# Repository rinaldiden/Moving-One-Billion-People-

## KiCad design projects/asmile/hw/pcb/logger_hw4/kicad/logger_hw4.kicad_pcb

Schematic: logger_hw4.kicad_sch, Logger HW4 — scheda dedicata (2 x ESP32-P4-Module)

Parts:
BZ1: buzzer attivo 3-7V; BUZ-SMD_L9.6-W9.6-LS10.0-R; LCSC C96127
C1, C2, C5, C8: 10u; C_0805_2012Metric; LCSC C15850
C3, C11, C21, C81, C91, C100, C101: 100n; C_0402_1005Metric; LCSC C1525
C4: 100n; C_0402_1005Metric; LCSC C1525; not fitted
C6, C7, C9, C10, C13, C20: 22u; C_0805_2012Metric; LCSC C45783
C12, C22, C37, C82, C92: 1u; C_0603_1608Metric; LCSC C1592
C36: 100n 50V; C_0603_1608Metric; LCSC C14663
C60, C70: 10u; C_0603_1608Metric; LCSC C19702
C80, C90: 4.7u; C_0402_1005Metric; LCSC C23733
D1: 1N4148W; SOD-123F_L2.7-W1.6-LS3.8-RD; LCSC C81598
D2: rosso; LED_0603_1608Metric; LCSC C2286
D3: verde; LED_0603_1608Metric; LCSC C12624
D4: blu (B); LED_0603_1608Metric; LCSC C2288
D5: SS34; SMA_L4.2-W2.6-LS5.0-RD_1; LCSC C8678
D6: SMF5.0A; SOD-123FL_L2.7-W1.8-LS3.8-RD; LCSC C193402
D8: SS14; SMA_L4.2-W2.6-LS5.0-RD_1; LCSC C2480
H1, H2, H3, H4: M2.5; MountingHole_2.7mm_M2.5
H11, H12, H13, H14, H15, H16, H17, H18: M2 camera; MountingHole_2.2mm_M2
J1: USB-C (carica + flash A); USB-C_SMD-TYPE-C-31-M-12_1; LCSC C165948
J2: BATT 1S 3 poli (+, NTC, -); CONN-SMD_S3B-PH-SM4-TB-LF-SN; LCSC C265101
J3: INTERRUTTORE est. (2 poli); CONN-SMD_PH-2AWT; LCSC C2763693
J11, J21: u.FL (piano B); RF-SMD_FRF05002-JSS103M; LCSC C88374; not fitted
J12: DEBUG A (UART0 37/38 + EN + BOOT, pogo); PinHeader_1x06_P2.54mm_Vertical; not fitted
J22: PROG B (UART0 37/38 + EN + BOOT, pogo); PinHeader_1x06_P2.54mm_Vertical; not fitted
J60: CAM SX FFC 15p 1mm; CONN-SMD_15P-P1.00_SHOU-HAN_1.0MM-15P-LT; LCSC C7529394
J61: TRIG A; CONN-SMD_2P-P1.00_SM02B-SRSS-TB-LF-SN; LCSC C160402
J70: CAM DX FFC 15p 1mm; CONN-SMD_15P-P1.00_SHOU-HAN_1.0MM-15P-LT; LCSC C7529394
J71: TRIG B; CONN-SMD_2P-P1.00_SM02B-SRSS-TB-LF-SN; LCSC C160402
J80: microSD A; TF-SMD_TF-015; LCSC C113206
J90: microSD B; TF-SMD_TF-015; LCSC C113206
J100: ESPANSIONE A; PinHeader_1x06_P2.54mm_Vertical; not fitted
L1, L2: 2.2u 4.5A; IND-SMD_L4.4-W4.2; LCSC C408335
Q1: FS8205A; SOT-23-6_L2.9-W1.6-P0.95-LS2.8-BL; LCSC C2830320
Q2: S8050; SOT-23_L2.9-W1.3-P1.90-LS2.4-BR; LCSC C2146
Q3, Q8, Q9: AO3401A; SOT-23-3_L3.0-W1.7-P0.95-LS2.9-BR; LCSC C15127
R1, R2: 5.1k; R_0402_1005Metric; LCSC C25905
R3, R4, R81, R91: 22; R_0402_1005Metric; LCSC C25092
R5: 1.2k; R_0402_1005Metric; LCSC C25862
R6, R35, R40, R41, R43, R44, R63, R73, R80, R82, R83, R84, R85, R86, R90, R92, R93, R94, R95, R96: 10k; R_0402_1005Metric; LCSC C25744
R7: 6.8k; R_0402_1005Metric; LCSC C25917
R8, R60, R70: 100; R_0402_1005Metric; LCSC C25076
R9, R50, R51, R52, R53, R54, R55, R100, R102, R103, R104: 1k; R_0402_1005Metric; LCSC C11702
R10, R13, R18, R20, R32, R101: 100k; R_0402_1005Metric; LCSC C25741
R11: 33k; R_0402_1005Metric; LCSC C25779
R12: 68k; R_0402_1005Metric; LCSC C36871
R19, R21: 22k; R_0402_1005Metric; LCSC C25768
R30, R33: 0; R_0402_1005Metric; LCSC C17168
R31, R34, R42, R45: 0; R_0402_1005Metric; LCSC C17168; not fitted
R36: 0 (PTC/perla); R_0805_2012Metric; LCSC C17477
R61, R62, R71, R72: 4.7k; R_0402_1005Metric; LCSC C25900
R110, R111, R112, R113, R114: 33; R_0402_1005Metric; LCSC C25105
RT1: NTC 10k B3950; R0805; LCSC C51597
SW1: BOOT A; SW-SMD_4P-L5.1-W5.1-P3.70-LS6.5-TL_H1.5; LCSC C318884
SW2: RESET A; SW-SMD_4P-L5.1-W5.1-P3.70-LS6.5-TL_H1.5; LCSC C318884
TP1: VBUS; TestPoint_Pad_D1.5mm
TP2: BATP; TestPoint_Pad_D1.5mm
TP3: VSYS; TestPoint_Pad_D1.5mm
TP4: 3V3_A; TestPoint_Pad_D1.5mm
TP5: 3V3_B; TestPoint_Pad_D1.5mm
TP6: GND; TestPoint_Pad_D1.5mm
TP7: VSYS_IN; TestPoint_Pad_D1.5mm
TP11: C6_RXD_A; TestPoint_Pad_D1.5mm
TP12: C6_TXD_A; TestPoint_Pad_D1.5mm
TP13: C6_BOOT_A; TestPoint_Pad_D1.5mm
TP21: C6_RXD_B; TestPoint_Pad_D1.5mm
TP22: C6_TXD_B; TestPoint_Pad_D1.5mm
TP23: C6_BOOT_B; TestPoint_Pad_D1.5mm
TP30: USB_DM_B; TestPoint_Pad_D1.5mm
TP31: USB_DP_B; TestPoint_Pad_D1.5mm
TP40: SYNC; TestPoint_Pad_D1.5mm
TP41: TRIG; TestPoint_Pad_D1.5mm
U1: USBLC6-2SC6; SOT-23-6_L2.9-W1.6-P0.95-LS2.8-BL; LCSC C2827654
U2: TP4056; ESOP-8_L4.9-W3.9-P1.27-LS6.0-BL-EP; LCSC C725790
U3: DW01A; SOT-23-6_L2.9-W1.6-P0.95-LS2.8-BR; LCSC C351410
U4, U5: TLV62569DBVR; SOT-23-5_L3.0-W1.7-P0.95-LS2.8-BR; LCSC C141836
U6: LSM6DS3TR-C; LGA-14_L3.0-W2.5-P0.50-TL; LCSC C967633
U7: AW32901 OVP 5,95 V; FCQFN-12_1.3x1.8mm_P0.4mm_AW32901; LCSC C407920
U10, U20: Waveshare ESP32-P4-Module (IPEX); Waveshare_ESP32-P4-Module

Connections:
3V3_A: C6.1, C7.1, C10.1, C11.1, C60.1, C100.1, C101.1, J12.6, J60.15, J100.1, L1.2, Q8.2 (S), R6.2, R18.1, R40.1, R41.1, R61.2, R62.2, R63.2, R80.2, TP4.1, U6.5 (VDDIO), U6.8 (VDD), U6.12 (CS), U10.84 (VBAT), U10.85 (ESP_3V3), U10.86 (ESP_3V3)
3V3_B: C9.1, C13.1, C20.1, C21.1, C70.1, J22.6, J70.15, L2.2, Q9.2 (S), R20.1, R43.1, R44.1, R71.2, R72.2, R73.2, R90.2, TP5.1, U20.84 (VBAT), U20.85 (ESP_3V3), U20.86 (ESP_3V3)
ANT_A: R42.1, U10.2 (LNA_OUT)
ANT_B: R45.1, U20.2 (LNA_OUT)
ANT_UFL_A: J11.1 (SIG), R42.2
ANT_UFL_B: J21.1 (SIG), R45.2
BATP: C2.1, J2.1, Q3.3 (D), R8.1, R10.1, TP2.1, U2.5 (BAT)
BATT_ADC: C4.1, R10.2, R11.1, U10.29 (GPIO20)
BAT_N: C3.2, J2.3, Q1.1 (S1), U3.6 (GND)
BOOT_A: J12.5, R41.2, SW1.1 (A), SW1.2 (B), U10.62 (GPIO35)
BOOT_B: J22.5, R44.2, R55.2, U20.62 (GPIO35)
BUZZER: R100.1, U10.54 (GPIO27)
BUZ_BASE: Q2.1 (B), R100.2, R101.1
BUZ_K: BZ1.2, D1.2 (A), Q2.3 (C)
B_BOOT_CTL: R55.1, U10.77 (GPIO49)
B_EN_CTL: R54.1, U10.60 (GPIO33)
B_PWR_EN: R31.1, U10.21 (GPIO6)
C6_BOOT_A: TP13.1, U10.9 (C6_IO9)
C6_BOOT_B: TP23.1, U20.9 (C6_IO9)
C6_RXD_A: TP11.1, U10.4 (C6_U0RXD)
C6_RXD_B: TP21.1, U20.4 (C6_U0RXD)
C6_TXD_A: TP12.1, U10.5 (C6_U0TXD)
C6_TXD_B: TP22.1, U20.5 (C6_U0TXD)
CAM_EN_A: J60.11, R63.1, U10.26 (GPIO11)
CAM_EN_B: J70.11, R73.1, U20.26 (GPIO11)
CC1: J1.A5 (CC1), R1.1
CC2: J1.B5 (CC2), R2.1
CHRG_N: R6.1, U2.7 (~CHRG), U10.53 (GPIO26)
CSI_CKN_A: J60.8, U10.44 (CSI_CLKN)
CSI_CKN_B: J70.8, U20.44 (CSI_CLKN)
CSI_CKP_A: J60.9, U10.43 (CSI_CLKP)
CSI_CKP_B: J70.9, U20.43 (CSI_CLKP)
CSI_D0N_A: J60.2, U10.41 (CSI_DATAN0)
CSI_D0N_B: J70.2, U20.41 (CSI_DATAN0)
CSI_D0P_A: J60.3, U10.42 (CSI_DATAP0)
CSI_D0P_B: J70.3, U20.42 (CSI_DATAP0)
CSI_D1N_A: J60.5, U10.45 (CSI_DATAN1)
CSI_D1N_B: J70.5, U20.45 (CSI_DATAN1)
CSI_D1P_A: J60.6, U10.46 (CSI_DATAP1)
CSI_D1P_B: J70.6, U20.46 (CSI_DATAP1)
EN_A: C12.1, J12.4, R40.2, SW2.1 (A), SW2.2 (B), U10.87 (ESP_EN)
EN_B: C22.1, J22.4, R43.2, R54.2, U20.87 (ESP_EN)
EN_BUCK_B: R30.2, R31.2, R32.1, U5.1 (EN)
EXP_IO1: J100.2, U10.16 (GPIO1)
EXP_IO47: J100.3, U10.75 (GPIO47)
EXP_IO48: J100.4, U10.76 (GPIO48)
FB_A: R18.2, R19.1, U4.5 (FB)
FB_B: R20.2, R21.1, U5.5 (FB)
GATE_Q3: D8.1 (K), Q3.1 (G), R35.1
GND: C1.2, C2.2, C4.2, C5.2, C6.2, C7.2, C8.2, C9.2, C10.2, C11.2, C12.2, C13.2, C20.2, C21.2, C22.2, C36.2, C37.2, C60.2, C70.2, C80.2, C81.2, C82.2, C90.2, C91.2, C92.2, C100.2, C101.2, D2.1 (K), D3.1 (K), D4.1 (K), D6.2 (A), J1.1 (EH), J1.2 (EH), J1.3 (EH), J1.4 (EH), J1.A1B12 (GND), J1.B1A12 (GND), J3.3, J3.4, J11.2 (GND), J11.3 (GND), J12.1, J21.2 (GND), J21.3 (GND), J22.1, J60.1, J60.4, J60.7, J60.10, J60.16, J60.17, J61.2, J61.3, J61.4, J70.1, J70.4, J70.7, J70.10, J70.16, J70.17, J71.2, J71.3, J71.4, J80.6 (VSS), J80.10 (GND), J80.11 (GND), J80.12 (GND), J80.13 (GND), J90.6 (VSS), J90.10 (GND), J90.11 (GND), J90.12 (GND), J90.13 (GND), J100.6, Q1.3 (S2), Q2.2 (E), R1.2, R2.2, R5.2, R9.2, R11.2, R13.2, R19.2, R21.2, R32.2, R35.2, R101.2, RT1.2, SW1.3 (C), SW1.4 (D), SW2.3 (C), SW2.4 (D), TP6.1, U1.2 (GND), U2.3 (GND), U2.9 (EP), U4.2 (GND), U5.2 (GND), U6.1 (SDO/SA0), U6.2 (SDx), U6.3 (SCx), U6.6 (GND), U6.7 (GND), U7.A1 (~EN), U7.A4 (GND), U7.B4 (GND), U7.C1 (OVLO), U7.C4 (GND), U10.1 (GND), U10.3 (GND), U10.15 (GND), U10.33 (GND), U10.40 (GND), U10.47 (GND), U10.52 (GND), U10.83 (GND), U20.1 (GND), U20.3 (GND), U20.15 (GND), U20.33 (GND), U20.40 (GND), U20.47 (GND), U20.52 (GND), U20.83 (GND)
I2C_SCL_A: J60.13, R62.1, U6.13 (SCL), U10.23 (GPIO8)
I2C_SCL_B: J70.13, R72.1, U20.23 (GPIO8)
I2C_SDA_A: J60.14, R61.1, U6.14 (SDA), U10.22 (GPIO7)
I2C_SDA_B: J70.14, R71.1, U20.22 (GPIO7)
IMU_INT: U6.4 (INT1), U10.19 (GPIO4)
LED_B: R104.1, U20.78 (GPIO50)
LED_B_R: D4.2 (A), R104.2
LED_G: R103.1, U10.80 (GPIO52)
LED_G_R: D3.2 (A), R103.2
LED_R: R102.1, U10.78 (GPIO50)
LED_R_R: D2.2 (A), R102.2
NTC_EXT: J2.2, R34.2
PROG: R5.1, U2.2 (PROG)
PROT_D: Q1.2 (D1/D2), Q1.5 (D1/D2)
PROT_OC: Q1.4 (G2), U3.3 (OC)
PROT_OD: Q1.6 (G1), U3.1 (OD)
PROT_VCC: C3.1, R8.2, U3.5 (VCC)
PROT_VM: R9.1, U3.2 (VM)
SD_CLK_A: J80.5 (CLK(SCLK)), R81.2
SD_CLK_B: J90.5 (CLK(SCLK)), R91.2
SD_CLK_M_A: R81.1, U10.71 (GPIO43)
SD_CLK_M_B: R91.1, U20.71 (GPIO43)
SD_CMD_A: J80.3 (CMD(DI)), R86.1, U10.72 (GPIO44)
SD_CMD_B: J90.3 (CMD(DI)), R96.1, U20.72 (GPIO44)
SD_D0_A: J80.7 (DAT0(D0)), R82.1, U10.67 (GPIO39)
SD_D0_B: J90.7 (DAT0(D0)), R92.1, U20.67 (GPIO39)
SD_D1_A: J80.8 (DAT1(RSV)), R83.1, U10.68 (GPIO40)
SD_D1_B: J90.8 (DAT1(RSV)), R93.1, U20.68 (GPIO40)
SD_D2_A: J80.1 (DAT2(RSV)), R84.1, U10.69 (GPIO41)
SD_D2_B: J90.1 (DAT2(RSV)), R94.1, U20.69 (GPIO41)
SD_D3_A: J80.2 (CDDAT3(CS)), R85.1, U10.70 (GPIO42)
SD_D3_B: J90.2 (CDDAT3(CS)), R95.1, U20.70 (GPIO42)
SD_PWR_N_A: Q8.1 (G), R80.1, U10.73 (GPIO45)
SD_PWR_N_B: Q9.1 (G), R90.1, U20.73 (GPIO45)
SD_VCC_A: C80.1, C81.1, J80.4 (VDD), Q8.3 (D)
SD_VCC_B: C90.1, C91.1, J90.4 (VDD), Q9.3 (D)
SPI_CS_A: R113.1, U10.58 (GPIO31)
SPI_CS_B: R113.2, U20.58 (GPIO31)
SPI_HS_A: R114.1, U10.59 (GPIO32)
SPI_HS_B: R114.2, U20.59 (GPIO32)
SPI_MISO_A: R112.1, U10.57 (GPIO30)
SPI_MISO_B: R112.2, U20.57 (GPIO30)
SPI_MOSI_A: R111.1, U10.56 (GPIO29)
SPI_MOSI_B: R111.2, U20.56 (GPIO29)
SPI_SCLK_A: R110.1, U10.55 (GPIO28)
SPI_SCLK_B: R110.2, U20.55 (GPIO28)
SW_A: L1.1, U4.3 (SW)
SW_B: L2.1, U5.3 (SW)
SYNC_B: R50.2, U20.30 (GPIO21)
SYNC_M: R50.1, TP40.1, U10.18 (GPIO3)
TEMP: R7.2, R33.1, R34.1, U2.1 (TEMP)
TEMP_NTC: R33.2, RT1.1
TRIG_A: J61.1, R60.2
TRIG_B: J71.1, R70.2
TRIG_M: R60.1, R70.1, TP41.1, U10.17 (GPIO2)
U0RXD_A: J12.3, U10.65 (GPIO38)
U0RXD_B: J22.3, U20.65 (GPIO38)
U0TXD_A: J12.2, U10.64 (GPIO37)
U0TXD_B: J22.2, U20.64 (GPIO37)
UART_AB: R52.1, U10.31 (GPIO22)
UART_AB_B: R52.2, U20.32 (GPIO23)
UART_BA: R53.2, U10.32 (GPIO23)
UART_BA_B: R53.1, U20.31 (GPIO22)
USB_DM_A: R3.2, U10.50 (GPIO24)
USB_DM_B: TP30.1, U20.50 (GPIO24)
USB_DM_C: J1.A7 (DN1), J1.B7 (DN2), R3.1, U1.1 (IO1), U1.6 (IO1)
USB_DP_A: R4.2, U10.51 (GPIO25)
USB_DP_B: TP31.1, U20.51 (GPIO25)
USB_DP_C: J1.A6 (DP1), J1.B6 (DP2), R4.1, U1.3 (IO2), U1.4 (IO2)
VBUS: C1.1, C37.1, D5.2 (A), D8.2 (A), R7.1, R12.1, TP1.1, U2.4 (VCC), U2.8 (CE), U7.A2 (OUT), U7.A3 (OUT), U7.B2 (OUT)
VBUS_C: J1.A4B9 (VBUS), J1.B4A9 (VBUS), R36.1
VBUS_RAW: C36.1, D6.1 (C), R36.2, U1.5 (VBUS), U7.B3 (IN), U7.C2 (IN), U7.C3 (IN)
VBUS_SENSE: R12.2, R13.1, U10.30 (GPIO21)
VDD_SDIO_A: C82.1, R82.2, R83.2, R84.2, R85.2, R86.2, U10.66 (ESP_LDO_VO4)
VDD_SDIO_B: C92.1, R92.2, R93.2, R94.2, R95.2, R96.2, U20.66 (ESP_LDO_VO4)
VSYS: BZ1.1, C5.1, C8.1, D1.1 (K), J3.2, J100.5, R30.1, TP3.1, U4.1 (EN), U4.4 (VIN), U5.4 (VIN)
VSYS_IN: D5.1 (K), J3.1, Q3.2 (S), TP7.1
WAKE_B: R51.2, U20.20 (GPIO5)
WAKE_M: R51.1, U10.20 (GPIO5)

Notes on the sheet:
ALIMENTAZIONE
MODULO A
MODULO B
A-B
CAMERA A
CAMERA B
SD A
SD B
SENSORI E SEGNALI
MECCANICA
LOGGER HW4 — schema generato da netlist_hw4.py (genera_schema.py). NON modificare a mano: si rigenera. Stessi GPIO di HW3 = firmware hw3-def invariato. Vedi DESIGN.md.

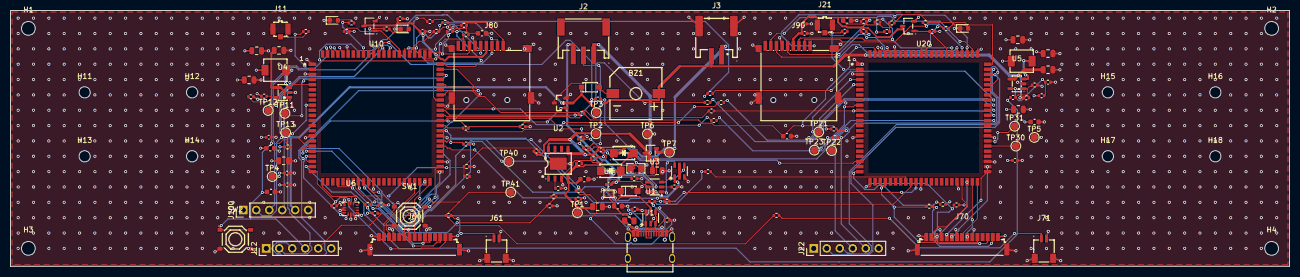
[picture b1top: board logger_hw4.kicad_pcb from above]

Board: 4 copper layers, 250.0 x 50.0 mm, 166 parts (0 on the bottom side), 129 nets.

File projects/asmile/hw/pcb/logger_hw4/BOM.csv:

designatori,qta,valore,footprint,LCSC,MPN,Basic/Extended,stock_2026-11-19,prezzo_10,prezzo_100,prezzo_1000,alternativa pin-compatibile,non montati (DNP)
BZ1,1,buzzer attivo 3-7V,BUZ-SMD_L9.6-W9.6-LS10.0-R,C96127,MLT-9650,Extended,19393,0.4259,0.3276,0.2392,"C409830 YS-SBZ9650DYB05 (9,6×9,6 mm)",
C1 C2 C5 C8,4,10u,C_0805_2012Metric,C15850,CL21A106KAYNNNE,Basic,8798581,0.0312,0.0312,0.02,,
C3 C11 C21 C81 C91 C100 C101,7,100n,C_0402_1005Metric,C1525,CL05B104KO5NNNC,Basic,35230048,0.0024,0.0024,0.0018,,C4
C36,1,100n 50V,C_0603_1608Metric,C14663,CC0603KRX7R9BB104,Basic,53069328,0.0049,0.0049,0.0039,,
C37 C12 C22 C82 C92,5,1u,C_0603_1608Metric,C1592,CL10A105KO8NNNC,Extended,7268995,0.0077,0.0077,0.0053,,
C6 C7 C9 C13 C10 C20,6,22u,C_0805_2012Metric,C45783,CL21A226MAQNNNE,Basic,3665575,0.1085,0.1085,0.0765,,
C60 C70,2,10u,C_0603_1608Metric,C19702,CL10A106KP8NNNC,Basic,10685417,0.0168,0.0168,0.0118,,
C80 C90,2,4.7u,C_0402_1005Metric,C23733,CL05A475MP5NRNC,Basic,1022537,0.0077,0.0077,0.006,,
D1,1,1N4148W,SOD-123F_L2.7-W1.6-LS3.8-RD,C81598,1N4148W,Basic,3003186,0.0124,0.0124,0.0097,1N4148W altri produttori,
D2,1,rosso,LED_0603_1608Metric,C2286,KT-0603R,Basic,8760151,0.0077,0.0077,0.0059,,
D3,1,verde,LED_0603_1608Metric,C12624,KT-0603G,Extended,208308,0.0119,0.0119,0.0093,,
D4,1,blu (B),LED_0603_1608Metric,C2288,KT-0603B,Extended,66147,0.0106,0.0106,0.0082,,
D5,1,SS34,SMA_L4.2-W2.6-LS5.0-RD_1,C8678,SS34,Basic,2556097,0.0351,0.0351,0.0251,,
D6,1,SMF5.0A,SOD-123FL_L2.7-W1.8-LS3.8-RD,C193402,SMF5.0A,Extended,454340,0.0284,0.0284,0.019,,
D8,1,SS14,SMA_L4.2-W2.6-LS5.0-RD_1,C2480,SS14,Basic,1261452,0.0192,0.0192,0.0152,,
J1,1,USB-C (carica + flash A),USB-C_SMD-TYPE-C-31-M-12_1,C165948,TYPE-C-31-M-12,Extended,505644,0.1871,0.1478,0.1042,C2765186 TYPE-C 16P 2MD(073) (stesso footprint? DA VERIFICARE),
,0,u.FL (piano B),RF-SMD_FRF05002-JSS103M,C88374,U.FL-R-SMT-1(80),Extended,286504,0.1091,0.089,0.0701,u.FL compatibili IPEX MHF1,J11 J21
J2,1,"BATT 1S 3 poli (+, NTC, -)",CONN-SMD_S3B-PH-SM4-TB-LF-SN,C265101,S3B-PH-SM4-TB(LF)(SN),Extended,21707,0.2644,0.2139,0.1655,,
J3,1,INTERRUTTORE est. (2 poli),CONN-SMD_PH-2AWT,C2763693,PH-2AWT,Extended,36152,0.0397,0.0313,0.0228,,
J60,1,CAM SX FFC 15p 1mm,CONN-SMD_15P-P1.00_SHOU-HAN_1.0MM-15P-LT,C7529394,1.0mm-15P LT,Extended,935,0.1175,0.0929,0.0806,"C23397372 FC-10A15P11H20 (15p 1 mm, contatti in basso: DA VERIFICARE lato contatti)",
J61,1,TRIG A,CONN-SMD_2P-P1.00_SM02B-SRSS-TB-LF-SN,C160402,SM02B-SRSS-TB(LF)(SN),Extended,33304,0.1324,0.109,0.087,C5306062 SM02B-SRSS-TB,
J70,1,CAM DX FFC 15p 1mm,CONN-SMD_15P-P1.00_SHOU-HAN_1.0MM-15P-LT,C7529394,1.0mm-15P LT,Extended,935,0.1175,0.0929,0.0806,"C23397372 FC-10A15P11H20 (15p 1 mm, contatti in basso: DA VERIFICARE lato contatti)",
J71,1,TRIG B,CONN-SMD_2P-P1.00_SM02B-SRSS-TB-LF-SN,C160402,SM02B-SRSS-TB(LF)(SN),Extended,33304,0.1324,0.109,0.087,C5306062 SM02B-SRSS-TB,
J80,1,microSD A,TF-SMD_TF-015,C113206,TF-015,Extended,31035,0.1296,0.1034,0.0793,C381082 XKTF-015-N (stesso ingombro TF-015),
J90,1,microSD B,TF-SMD_TF-015,C113206,TF-015,Extended,31035,0.1296,0.1034,0.0793,C381082 XKTF-015-N (stesso ingombro TF-015),
L1 L2,2,2.2u 4.5A,IND-SMD_L4.4-W4.2,C408335,MWSA0402S-2R2MT,Extended,19504,0.1445,0.1186,0.0962,"qualsiasi 2,2 µH ≥2,5 A 4×4 mm (es. FNR4030S2R2M) — controllare l'ingombro",
Q1,1,FS8205A,SOT-23-6_L2.9-W1.6-P0.95-LS2.8-BL,C2830320,FS8205A,Extended,164776,0.05,0.038,0.0322,C908265 FS8205A (SOT-23-6) · 8205A di altri produttori,
Q2,1,S8050,SOT-23_L2.9-W1.3-P1.90-LS2.4-BR,C2146,S8050 J3Y(RANGE:200-350),Basic,958439,0.0142,0.0142,0.0109,C105433 S8050,
Q3 Q8 Q9,3,AO3401A,SOT-23-3_L3.0-W1.7-P0.95-LS2.9-BR,C15127,AO3401A,Basic,1378074,0.0814,0.0641,0.0479,C347476 AO3401A,
R1 R2,2,5.1k,R_0402_1005Metric,C25905,0402WGF5101TCE,Basic,4377157,0.0014,0.0014,0.0011,,
R10 R13 R18 R20 R32 R101,6,100k,R_0402_1005Metric,C25741,0402WGF1003TCE,Basic,8665708,0.0009,0.0009,0.0007,,
R11,1,33k,R_0402_1005Metric,C25779,0402WGF3302TCE,Basic,2071363,0.0019,0.0019,0.0015,,
R110 R111 R112 R113 R114,5,33,R_0402_1005Metric,C25105,0402WGF330JTCE,Basic,4298285,0.0011,0.0011,0.0009,,
R12,1,68k,R_0402_1005Metric,C36871,0402WGF6802TCE,Extended,1079907,0.0012,0.0012,0.0009,,
R19 R21,2,22k,R_0402_1005Metric,C25768,0402WGF2202TCE,Basic,1190761,0.001,0.001,0.0008,,
R3 R4 R81 R91,4,22,R_0402_1005Metric,C25092,0402WGF220JTCE,Basic,4458426,0.001,0.001,0.0008,,
R33 R30,2,0,R_0402_1005Metric,C17168,0402WGF0000TCE,Basic,14591291,0.0012,0.0012,0.0009,,R34 R31 R42 R45
R36,1,0 (PTC/perla),R_0805_2012Metric,C17477,0805W8F0000T5E,Basic,4345708,0.0046,0.0046,0.0036,,
R5,1,1.2k,R_0402_1005Metric,C25862,0402WGF1201TCE,Extended,756536,0.0012,0.0012,0.0009,,
R6 R35 R40 R41 R43 R44 R63 R73 R80 R82 R83 R84 R85 R86 R90 R92 R93 R94 R95 R96,20,10k,R_0402_1005Metric,C25744,0402WGF1002TCE,Basic,36552394,0.0015,0.0015,0.0011,,
R61 R62 R71 R72,4,4.7k,R_0402_1005Metric,C25900,0402WGF4701TCE,Basic,12935079,0.0017,0.0017,0.0013,,
R7,1,6.8k,R_0402_1005Metric,C25917,0402WGF6801TCE,Extended,986615,0.0012,0.0012,0.0009,,
R8 R60 R70,3,100,R_0402_1005Metric,C25076,0402WGF1000TCE,Basic,10273753,0.0012,0.0012,0.001,,
R9 R50 R51 R52 R53 R54 R55 R100 R102 R103 R104,11,1k,R_0402_1005Metric,C11702,0402WGF1001TCE,Basic,30286284,0.0013,0.0013,0.0011,,
RT1,1,NTC 10k B3950,R0805,C51597,CMFB103F3950FANT,Extended,27248,0.0674,0.0534,0.0412,,
SW1,1,BOOT A,SW-SMD_4P-L5.1-W5.1-P3.70-LS6.5-TL_H1.5,C318884,TS-1187A-B-A-B,Basic,762703,0.0215,0.0215,0.0147,C42420254 TS-1187A,
SW2,1,RESET A,SW-SMD_4P-L5.1-W5.1-P3.70-LS6.5-TL_H1.5,C318884,TS-1187A-B-A-B,Basic,762703,0.0215,0.0215,0.0147,C42420254 TS-1187A,
U1,1,USBLC6-2SC6,SOT-23-6_L2.9-W1.6-P0.95-LS2.8-BL,C2827654,USBLC6-2SC6,Extended,206033,0.0449,0.0358,0.0312,C7519 USBLC6-2SC6 ST (originale) · C2687116,
U2,1,TP4056,ESOP-8_L4.9-W3.9-P1.27-LS6.0-BL-EP,C725790,TP4056,Extended,305414,0.0772,0.061,0.0457,"C16581 TP4056-42-ESOP8 (stesso pinout, altro produttore) · IP2312 NO (pinout diverso)",
U3,1,DW01A,SOT-23-6_L2.9-W1.6-P0.95-LS2.8-BR,C351410,DW01A,Extended,84491,0.0533,0.0533,0.0351,"C2927799 / C18164398 DW01A di altri produttori (SOT-23-6, stesso pinout)",
U4 U5,2,TLV62569DBVR,SOT-23-5_L3.0-W1.7-P0.95-LS2.8-BR,C141836,TLV62569DBVR,Extended,535714,0.0675,0.0533,0.0398,C47117578 TLV62569DBVR-TP (MCC) · C54839595 (stesso SOT-23-5 EN/GND/SW/VIN/FB),
U6,1,LSM6DS3TR-C,LGA-14_L3.0-W2.5-P0.50-TL,C967633,LSM6DS3TR-C,Extended,13883,1.1465,0.8615,0.7862,"nessuna pin-compatibile esatta in LGA-14 2,5×3 con stessi pin: piano B ICM-42670-P C3288646 (richiede footprint dedicato) → footprint opzionale",
U7,1,"AW32901 OVP 5,95 V",FCQFN-12_1.3x1.8mm_P0.4mm_AW32901,C407920,AW32901FCR,Extended,9526,0.3104,0.241,0.1741,,
"U10,U20",2,Waveshare ESP32-P4-Module 16MB (IPEX),,,,fornito a parte,,10.99,9.99,9.99,,"waveshare.com 9,99-10,99 $ (prezzo a 100 DA VERIFICARE: preventivo Waveshare); non in libreria JLC: kit consegnato o saldato a mano"
ANT,2,"antenna FPC 2,4 GHz IPEX adesiva",,,,fornito a parte,,1.0,0.6,0.4,,"stima, DA VERIFICARE"

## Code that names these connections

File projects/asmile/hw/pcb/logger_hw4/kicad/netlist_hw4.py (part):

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P("RT1", "CMFB103F3950FANT", "NTC 10k B3950", "R0805", "C51597", {"1": "TEMP_NTC", "2": "GND"}, blocco=B,
  nota="NTC sulla scheda accanto al portabatteria (temperatura cella/case)")
R("R33", "0", "TEMP", "TEMP_NTC", RES["0"], blocco=B, nota="montata: NTC sulla scheda")
R("R34", "0", "TEMP", "NTC_EXT", RES["0"], dnp=True, blocco=B, nota="piano B: NTC del pacco su J2 pin 2 (togliere R33)")
# TVS su VBUS (oltre all'USBLC6): SMF5.0A 200 W
P("D6", "SMF5.0A_C193402", "SMF5.0A", "SOD-123FL_L2.7-W1.8-LS3.8-RD", "C193402", {"1": "VBUS_RAW", "2": "GND"}, blocco=B,
  nota="TVS 5 V su VBUS: picchi da caricatori/cavi lunghi")
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R("R9", "1k", "PROT_VM", "GND", RES["1k"], blocco=B, nota="VM verso P- (= GND della scheda)")
P("Q1", "FS8205A_C2830320", "FS8205A", "SOT-23-6_L2.9-W1.6-P0.95-LS2.8-BL", "C2830320",
  {"1": "BAT_N", "2": "PROT_D", "5": "PROT_D", "3": "GND", "6": "PROT_OD", "4": "PROT_OC"}, blocco=B)
# interruttore esterno (quello di HW3) sul cavo: JST 2 pin, BATP → VSYS
# power-path (carico e carica separati): con USB la scheda va da VBUS via D5, la cella si carica da sola e il TP4056
# termina davvero a C/10; senza USB Q3 (P-MOS) conduce dalla cella. Interruttore DOPO l'OR: spento = spento anche in carica.
P("Q3", "AO3401A", "AO3401A", "SOT-23-3_L3.0-W1.7-P0.95-LS2.9-BR", "C15127",
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P("J3", "PH-2AWT", "INTERRUTTORE est. (2 poli)", "CONN-SMD_PH-2AWT", "C2763693",
  {"1": "VSYS_IN", "2": "VSYS", "3": "GND", "4": "GND"}, blocco=B,
  nota="2 poli ≠ J2 (3 poli): non invertibili. Senza interruttore: ponticello sul connettore")
# partitore batteria (HW3: 100k/33k su GPIO20)
R("R10", "100k", "BATP", "BATT_ADC", RES["100k"], blocco=B, nota="100k/33k come HW3: la sequenza di leggi_batteria() (pull-down 2 ms + 2 ms) è tarata su questa impedenza (modello_partitore.py)")
R("R11", "33k", "BATT_ADC", "GND", RES["33k"], blocco=B)
C("C4", "100n", "BATT_ADC", blocco=B, dnp=True, nota="NON montare con il firmware hw3-def: con 100 nF la lettura sbaglia (VETO 2, A11)")
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    C("C%d" % ca, "10u", "VSYS", fp=C0805, lcsc="C15850", blocco=B)
    C("C%d" % cb, "22u", "3V3_" + s, fp=C0805, lcsc="C45783", blocco=B)
    C("C%d" % cc, "22u", "3V3_" + s, fp=C0805, lcsc="C45783", blocco=B)
# EN del buck B: di serie da VSYS (B sempre accesa come HW3); piano B: da A GPIO6 (spegne B a zero consumo)
R("R30", "0", "VSYS", "EN_BUCK_B", RES["0"], blocco=B, nota="montata: B accesa con A")
R("R31", "0", "B_PWR_EN", "EN_BUCK_B", RES["0"], dnp=True, blocco=B, nota="piano B: A comanda l'alimentazione di B")
R("R32", "100k", "EN_BUCK_B", "GND", RES["100k"], blocco=B)
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    C("C%d" % (n + 1), "100n", "3V3_" + s, blocco=b)
    C("C%d" % (n + 2), "1u", "EN_" + s, fp=C0603, lcsc="C1592", blocco=b)
    R("R%d" % r0, "10k", "3V3_" + s, "EN_" + s, RES["10k"], blocco=b, nota="CHIP_PU RC 10k/1u (checklist P4 §Reset)")
    R("R%d" % (r0 + 1), "10k", "3V3_" + s, "BOOT_" + s, RES["10k"], blocco=b, nota="GPIO35 pull-up (strapping)")
    # antenna: versione IPEX del modulo → niente; piano B u.FL sulla scheda (non montato)
    R("R%d" % (r0 + 2), "0", "ANT_" + s, "ANT_UFL_" + s, RES["0"], dnp=True, blocco=b)
    P("J%d" % (n + 1), "U.FL-R-SMT-1", "u.FL (piano B)", "RF-SMD_FRF05002-JSS103M", "C88374",
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
# ---------------------------------------------------------------- collegamenti A ↔ B (piste, non più fili)
B = "A-B"
R("R50", "1k", "SYNC_M", "SYNC_B", RES["1k"], blocco=B, nota="SYNC 1 Hz A GPIO3 → B GPIO21 (HW3)")
R("R51", "1k", "WAKE_M", "WAKE_B", RES["1k"], blocco=B, nota="WAKE A GPIO5 → B GPIO5 (HW3)")
R("R52", "1k", "UART_AB", "UART_AB_B", RES["1k"], blocco=B, nota="A GPIO22 TX → B GPIO23 RX")
R("R53", "1k", "UART_BA_B", "UART_BA", RES["1k"], blocco=B, nota="B GPIO22 TX → A GPIO23 RX")
R("R54", "1k", "B_EN_CTL", "EN_B", RES["1k"], blocco=B, nota="A GPIO33 (open-drain) resetta B")
R("R55", "1k", "B_BOOT_CTL", "BOOT_B", RES["1k"], blocco=B, nota="A GPIO49 (open-drain) mette B in download")
for i, sig in enumerate(("SCLK", "MOSI", "MISO", "CS", "HS")):
    R("R%d" % (110 + i), "33", "SPI_%s_A" % sig, "SPI_%s_B" % sig, RES["33"], blocco=B,
      nota="SPI A↔B per il video della B verso la SD della A (firmware futuro)")
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       "6": "GND", "7": "SD_D0_" + s, "8": "SD_D1_" + s, "10": "GND", "11": "GND", "12": "GND", "13": "GND"},
      blocco=b)
    P("Q%d" % (n // 10), "AO3401A", "AO3401A", "SOT-23-3_L3.0-W1.7-P0.95-LS2.9-BR", "C15127",
      {"1": "SD_PWR_N_" + s, "2": "3V3_" + s, "3": "SD_VCC_" + s}, blocco=b, nota="GPIO45 basso = SD accesa (come la dev-kit)")
    R("R%d" % n, "10k", "SD_PWR_N_" + s, "3V3_" + s, RES["10k"], blocco=b)
    R("R%d" % (n + 1), "22", "SD_CLK_M_" + s, "SD_CLK_" + s, RES["22"], blocco=b)
    for i, sig in enumerate(("D0", "D1", "D2", "D3", "CMD")):
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P("U6", "LSM6DS3TR-C", "LSM6DS3TR-C", "LGA-14_L3.0-W2.5-P0.50-TL", "C967633",
  {"1": "GND", "2": "GND", "3": "GND", "4": "IMU_INT", "5": "3V3_A", "6": "GND", "7": "GND", "8": "3V3_A",
   "12": "3V3_A", "13": "I2C_SCL_A", "14": "I2C_SDA_A"}, blocco=B,
  nota="I2C 0x6A (SA0 a GND), CS alto = I2C; SDx/SCx a GND (aux non usato), INT1 → GPIO4 risveglio. NON è un MPU6050: il driver IMU del firmware va portato (unico cambio sw)")
C("C100", "100n", "3V3_A", blocco=B)
C("C101", "100n", "3V3_A", blocco=B)
P("BZ1", "HND-9650B", "buzzer attivo 3-7V", "BUZ-SMD_L9.6-W9.6-LS10.0-R", "C96127",
  {"1": "VSYS", "2": "BUZ_K"}, blocco=B, nota="sul pin del PA di HW3 (GPIO53): il saluto diventa un bip")
P("Q2", "S8050_C2146", "S8050", "SOT-23_L2.9-W1.3-P1.90-LS2.4-BR", "C2146",
  {"1": "BUZ_BASE", "2": "GND", "3": "BUZ_K"}, blocco=B)
R("R100", "1k", "BUZZER", "BUZ_BASE", RES["1k"], blocco=B)
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    R("R%d" % (102 + i), "1k", net, net + "_R", RES["1k"], blocco=B)
P("J100", "Conn_01x06", "ESPANSIONE A", "PinHeader_1x06_P2.54mm_Vertical", "",
  {"1": "3V3_A", "2": "EXP_IO1", "3": "EXP_IO47", "4": "EXP_IO48", "5": "VSYS", "6": "GND"}, dnp=True, blocco=B,
  nota="GPIO liberi della A. GPIO1 = XTAL_32K_P, GPIO47/48 nel dominio VDD_IO_5 (tensione della SD): verificare prima di usarli")
for i, net in enumerate(("VBUS", "BATP", "VSYS", "3V3_A", "3V3_B", "GND", "VSYS_IN")):
    P("TP%d" % (1 + i), "TestPoint", net, "TestPoint_Pad_D1.5mm", "", {"1": net}, blocco=B)
for i in range(4):
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
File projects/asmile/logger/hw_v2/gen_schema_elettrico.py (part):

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# ===== 6. RASPBERRY PI 5 =====
frame(1100, 310, 480, 520, "6 · Raspberry Pi 5 — header 40 pin")
blk(1270, 350, 160, 440, "#ebfbee", "#2f9e44", "RASPBERRY PI 5", "pin 1 = bollino quadrato")
pinsL = [(1, "3V3", "3V3_PI"), (3, "GPIO2 SDA", "SDA"), (5, "GPIO3 SCL", "SCL"), (15, "GPIO22", "LED_R"), (37, "GPIO26", "HOLD"), (39, "GND", "GND")]
pinsR = [(2, "5V", "5V"), (4, "5V", "5V"), (6, "GND", "GND"), (16, "GPIO23", "LED_G"), (18, "GPIO24", "LED_B")]
y = 410
for n, nm_, net in pinsL:
    pin(1270, y, f"{n} · {nm_}", "l")
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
